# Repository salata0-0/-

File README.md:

**Technical rehabilitation aid**

This is my diploma project.

I hope to one day be able to develop it into a fully funcioning product.

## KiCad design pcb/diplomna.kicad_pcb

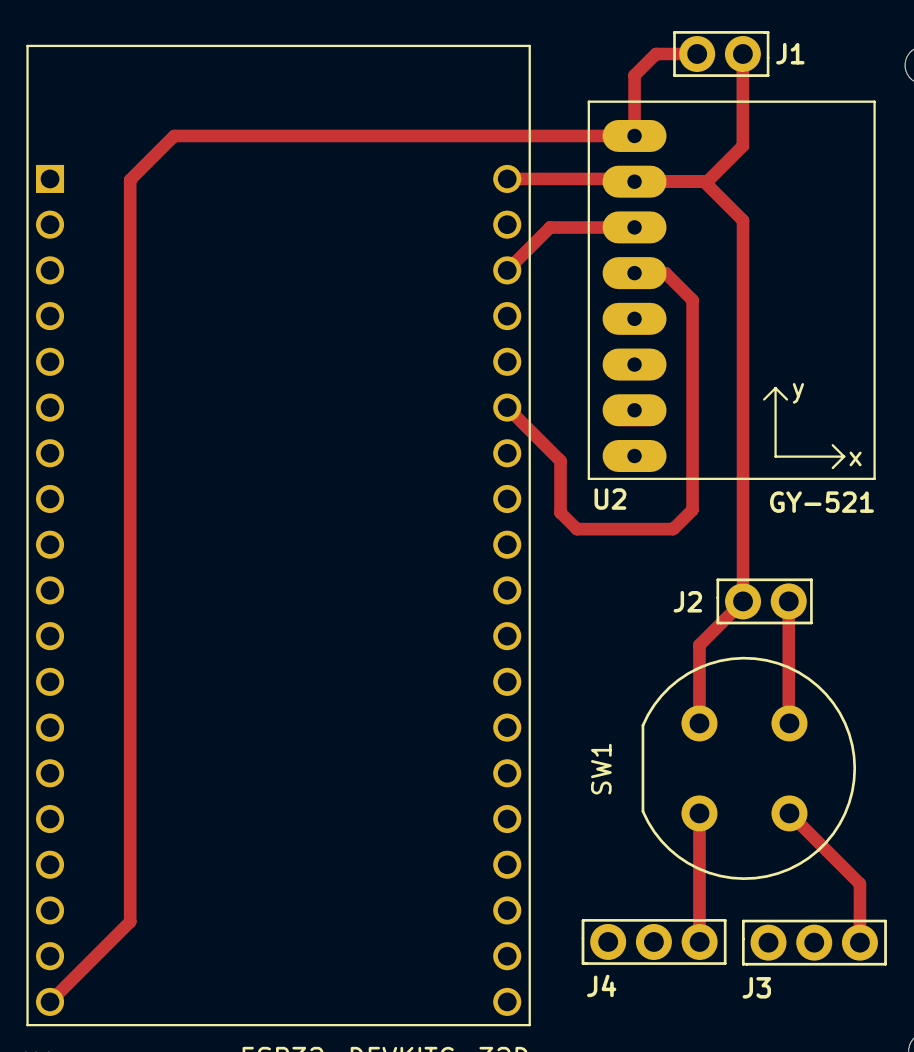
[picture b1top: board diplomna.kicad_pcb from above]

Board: 2 copper layers, 7 parts (0 on the bottom side), 7 nets.

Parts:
J1, J2: Conn_01x02; CONN_01x02
J3, J4: Conn_01x03; CONN_01x02
SW1: SW_Push_LED; Push_E-Switch_KS01Q01
U1: ESP32-DEVKITC-32D; MODULE_ESP32-DEVKITC-32D
U2: GY-521

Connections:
unnamed: J1.2 (GND), U1.J2-19 (5V), U2.1 (VCC)
unnamed: J1.1 (VCC), J2.1 (VCC), SW1.3 (K), U1.J3-1 (GND), U2.2 (GND)
unnamed: J2.2 (GND), SW1.1
unnamed: J3.3, SW1.2
unnamed: J4.3, SW1.4 (A)
unnamed: U1.J3-6 (IO21), U2.4 (SDA)
unnamed: U1.J3-3 (IO22), U2.3 (SCL)

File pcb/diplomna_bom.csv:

"Id";"Designator";"Footprint";"Quantity";"Designation";"Supplier and ref";
1;"U1";"MODULE_ESP32-DEVKITC-32D";1;"ESP32-DEVKITC-32D";;;
2;"J1,J2";"CONN_01x02";2;"Conn_01x02";;;
3;"U2";"GY-521";1;"GY-521";;;
4;"S1";"Push_E-Switch_KS01Q01";1;"SWITCH";;;
